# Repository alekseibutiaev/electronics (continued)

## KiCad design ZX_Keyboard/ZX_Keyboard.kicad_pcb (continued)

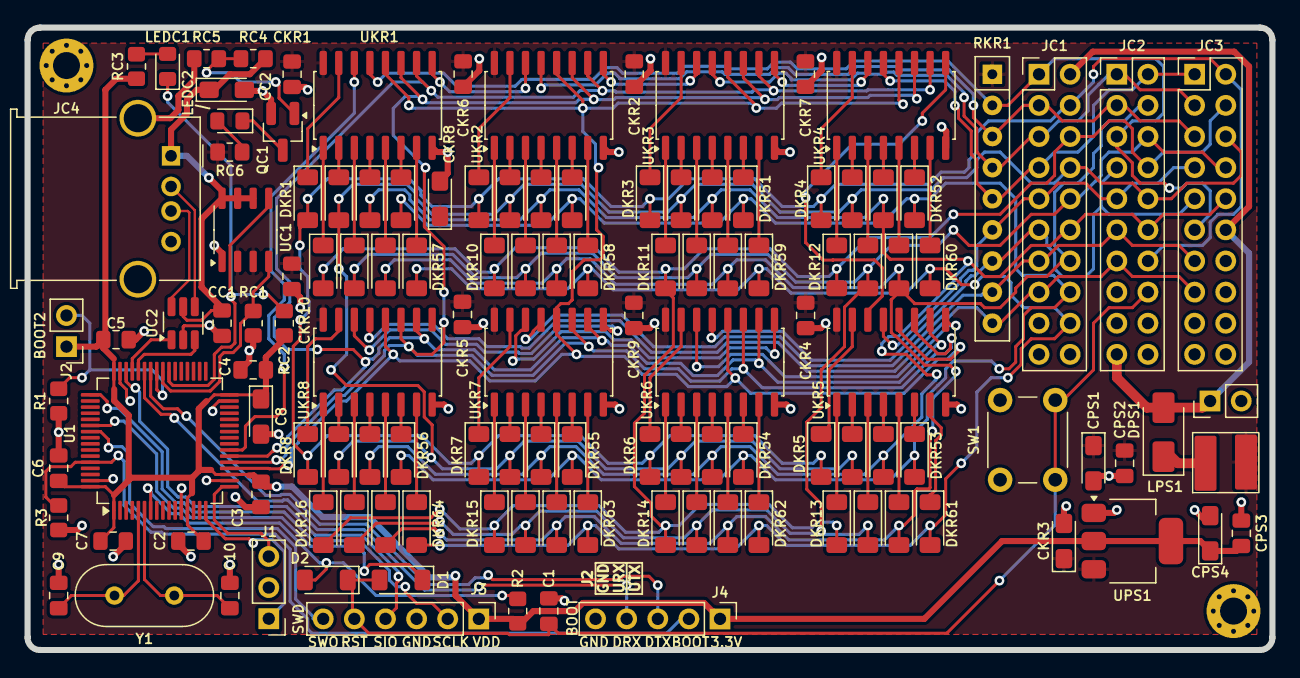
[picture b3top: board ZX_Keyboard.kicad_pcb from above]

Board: 2 copper layers, 101.6 x 50.8 mm, 132 parts (0 on the bottom side), 121 nets.

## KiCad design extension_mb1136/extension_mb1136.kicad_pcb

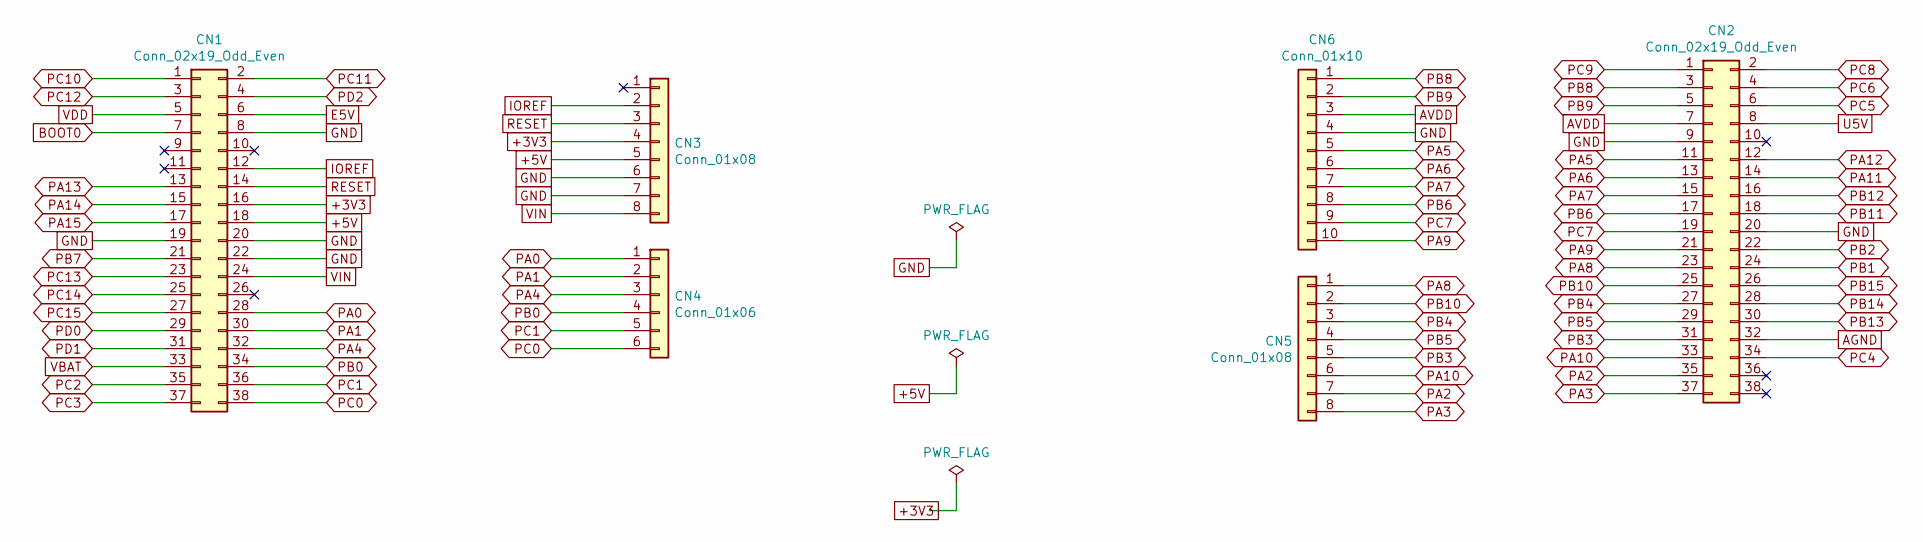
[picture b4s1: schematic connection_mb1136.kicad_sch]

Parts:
CN1, CN2: Conn_02x19_Odd_Even; PinHeader_2x19_P2.54mm_Vertical
CN3, CN5: Conn_01x08; PinSocket_1x08_P2.54mm_Vertical
CN4: Conn_01x06; PinSocket_1x06_P2.54mm_Vertical
CN6: Conn_01x10; PinSocket_1x10_P2.54mm_Vertical

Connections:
+3V3: CN1.16, CN3.4; also elsewhere on the board
+5V: CN1.18, CN3.5; also elsewhere on the board
AGND: CN2.32
AVDD: CN2.7, CN6.3
BOOT0: CN1.7
E5V: CN1.6
GND: CN1.8, CN1.19, CN1.20, CN1.22, CN2.9, CN2.20, CN3.6, CN3.7, CN6.4; also elsewhere on the board
IOREF: CN1.12, CN3.2
PA0: CN1.28, CN4.1
PA1: CN1.30, CN4.2
PA2: CN2.35, CN5.7
PA3: CN2.37, CN5.8
PA4: CN1.32, CN4.3
PA5: CN2.11, CN6.5
PA6: CN2.13, CN6.6
PA7: CN2.15, CN6.7
PA8: CN2.23, CN5.1
PA9: CN2.21, CN6.10; also elsewhere on the board
PA10: CN2.33, CN5.6
PA11: CN2.14; also elsewhere on the board
PA12: CN2.12; also elsewhere on the board
PA13: CN1.13
PA14: CN1.15
PA15: CN1.17
PB0: CN1.34, CN4.4
PB1: CN2.24
PB2: CN2.22
PB3: CN2.31, CN5.5
PB4: CN2.27, CN5.3
PB5: CN2.29, CN5.4
PB6: CN2.17, CN6.8
PB7: CN1.21
PB8: CN2.3, CN6.1
PB9: CN2.5, CN6.2
PB10: CN2.25, CN5.2; also elsewhere on the board
PB11: CN2.18
PB12: CN2.16
PB13: CN2.30
PB14: CN2.28
PB15: CN2.26
PC0: CN1.38, CN4.6
PC1: CN1.36, CN4.5
PC2: CN1.35
PC3: CN1.37
PC4: CN2.34
PC5: CN2.6
PC6: CN2.4
PC7: CN2.19, CN6.9
PC8: CN2.2; also elsewhere on the board
PC9: CN2.1; also elsewhere on the board
PC10: CN1.1
PC11: CN1.2
PC12: CN1.3
PC13: CN1.23
PC14: CN1.25
PC15: CN1.27
PD0: CN1.29
PD1: CN1.31
PD2: CN1.4
RESET: CN1.14, CN3.3
U5V: CN2.8
VBAT: CN1.33
VDD: CN1.5
VIN: CN1.24, CN3.8

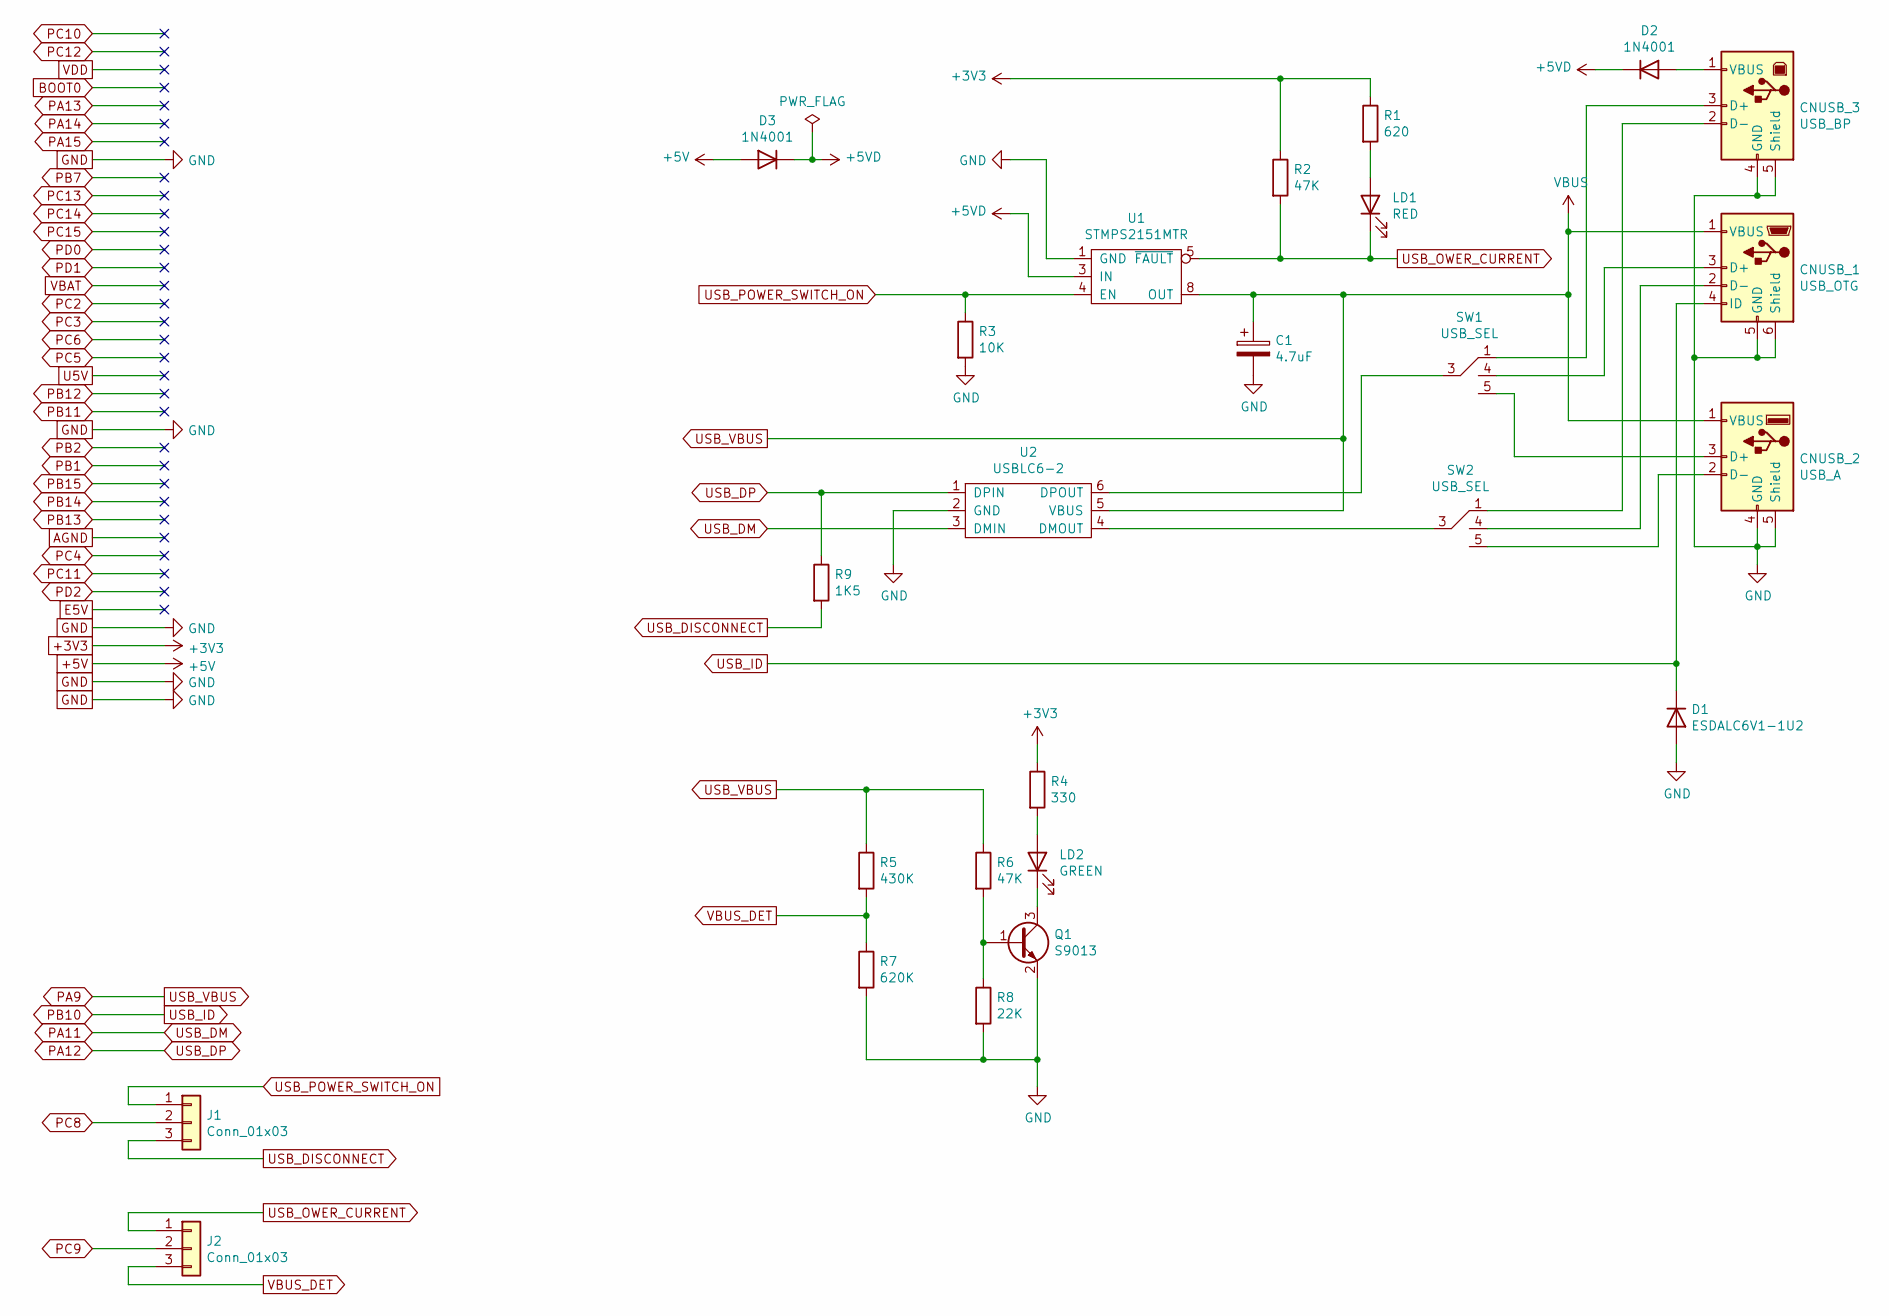
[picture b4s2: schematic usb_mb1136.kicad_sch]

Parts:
C1: 4.7uF; C_1206_3216Metric_Pad1.33x1.80mm_HandSolder
CNUSB_1: USB_OTG; USB_Micro-B_Molex-105017-0001
CNUSB_2: USB_A; USB_A_Molex_67643_Horizontal
CNUSB_3: USB_BP; USB_B_OST_USB-B1HSxx_Horizontal
D1: ESDALC6V1-1U2; D_0201_0603Metric
D2, D3: 1N4001; D_SOD-323_HandSoldering
J1, J2: Conn_01x03; PinHeader_1x03_P2.54mm_Vertical
LD1: RED; D_0805_2012Metric
LD2: GREEN; D_0805_2012Metric
Q1: S9013; SOT-23
R1: 620; R_0805_2012Metric
R2, R6: 47K; R_0805_2012Metric
R3: 10K; R_0805_2012Metric
R4: 330; R_0805_2012Metric
R5: 430K; R_0805_2012Metric
R7: 620K; R_0805_2012Metric
R8: 22K; R_0805_2012Metric
R9: 1K5; R_0805_2012Metric
SW1, SW2: USB_SEL; PinHeader_2x03_P2.54mm_Vertical
U1: STMPS2151MTR; SO-8_3.9x4.9mm_P1.27mm
U2: USBLC6-2; SOT-23-6_Handsoldering

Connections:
+3V3: R1.1, R2.1, R4.1; also elsewhere on the board
+5V: D3.2 (A); also elsewhere on the board
+5VD: D2.1 (K), D3.1 (K), U1.2 (IN), U1.3 (IN)
GND: C1.2, CNUSB_1.5 (GND), CNUSB_1.6 (Shield), CNUSB_2.4 (GND), CNUSB_2.5 (Shield), CNUSB_3.4 (GND), CNUSB_3.5 (Shield), D1.2 (A), Q1.2 (E), R3.2, R7.2, R8.2, U1.1 (GND), U2.2 (GND); also elsewhere on the board
unnamed: CNUSB_1.2 (D-), SW2.4
unnamed: CNUSB_1.3 (D+), SW1.4
unnamed: CNUSB_2.2 (D-), SW2.5
unnamed: CNUSB_2.3 (D+), SW1.5
unnamed: CNUSB_3.1 (VBUS), D2.2 (A)
unnamed: CNUSB_3.2 (D-), SW2.1
unnamed: CNUSB_3.3 (D+), SW1.1
unnamed: LD1.2 (A), R1.2
unnamed: LD2.1 (K), Q1.3 (C)
unnamed: LD2.2 (A), R4.2
unnamed: Q1.1 (B), R6.2, R8.1
unnamed: SW1.3, U2.6 (DPOUT)
unnamed: SW2.3, U2.4 (DMOUT)
PA9: C1.1, CNUSB_1.1 (VBUS), CNUSB_2.1 (VBUS), R5.1, R6.1, U1.6 (OUT), U1.7 (OUT), U1.8 (OUT), U2.5 (VBUS); also elsewhere on the board
PA11: U2.3 (DMIN); also elsewhere on the board
PA12: R9.1, U2.1 (DPIN); also elsewhere on the board
PB10: CNUSB_1.4 (ID), D1.1 (K); also elsewhere on the board
PC8: J1.2; also elsewhere on the board
PC9: J2.2; also elsewhere on the board
USB_DISCONNECT: J1.3, R9.2
USB_OWER_CURRENT: J2.1, LD1.1 (K), R2.2, U1.5 (~FAULT)
USB_POWER_SWITCH_ON: J1.1, R3.1, U1.4 (EN)
VBUS_DET: J2.3, R5.2, R7.1

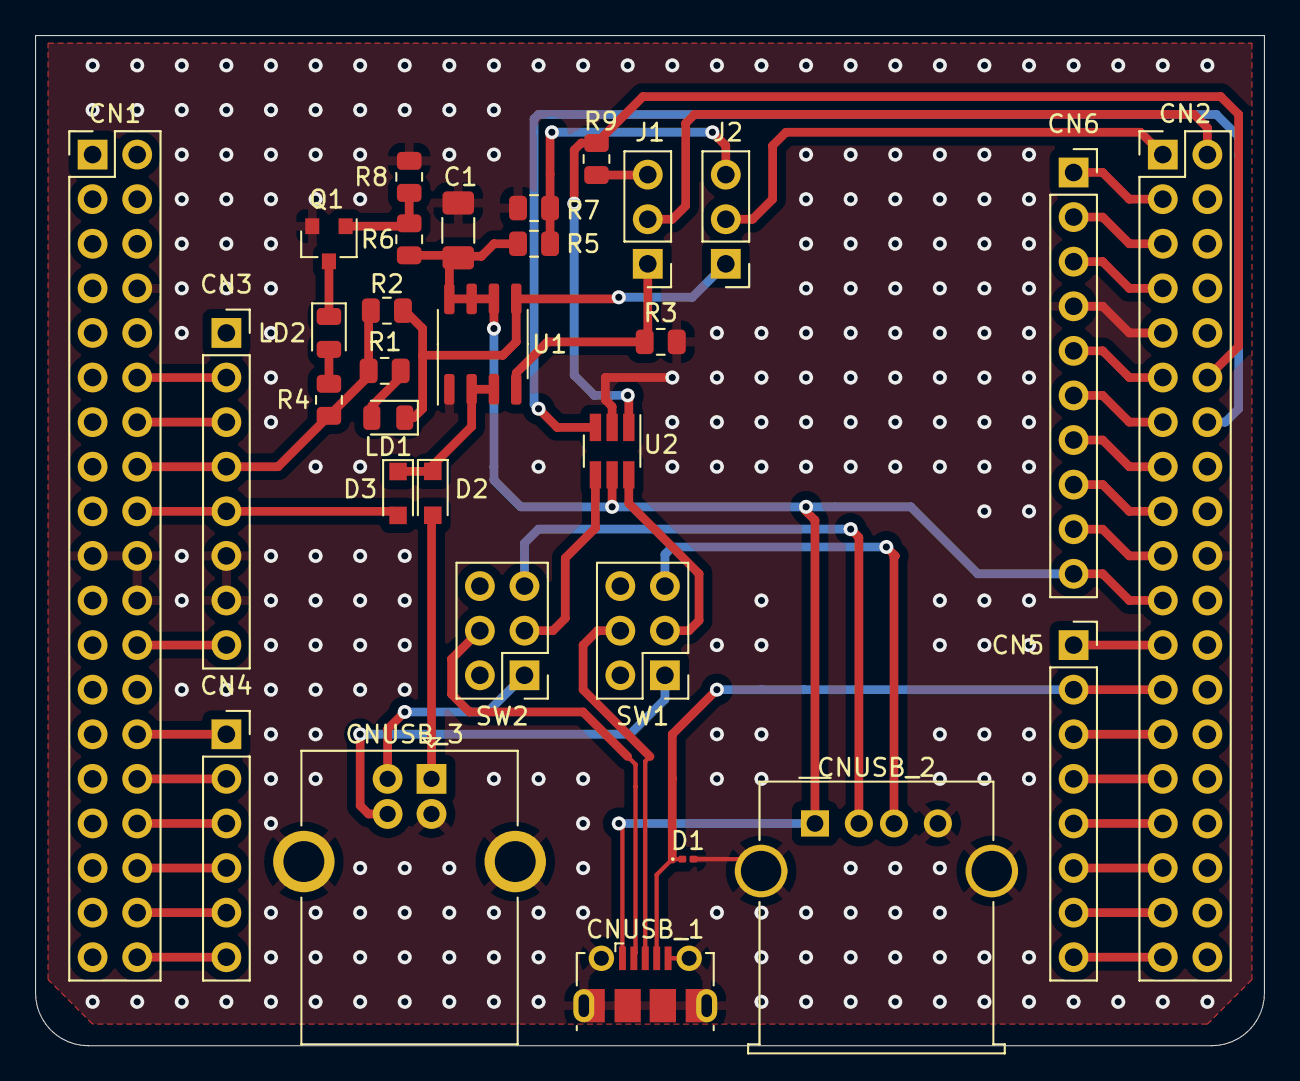
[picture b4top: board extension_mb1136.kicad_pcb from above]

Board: 2 copper layers, 70.0 x 57.5 mm, 31 parts (0 on the bottom side), 51 nets.

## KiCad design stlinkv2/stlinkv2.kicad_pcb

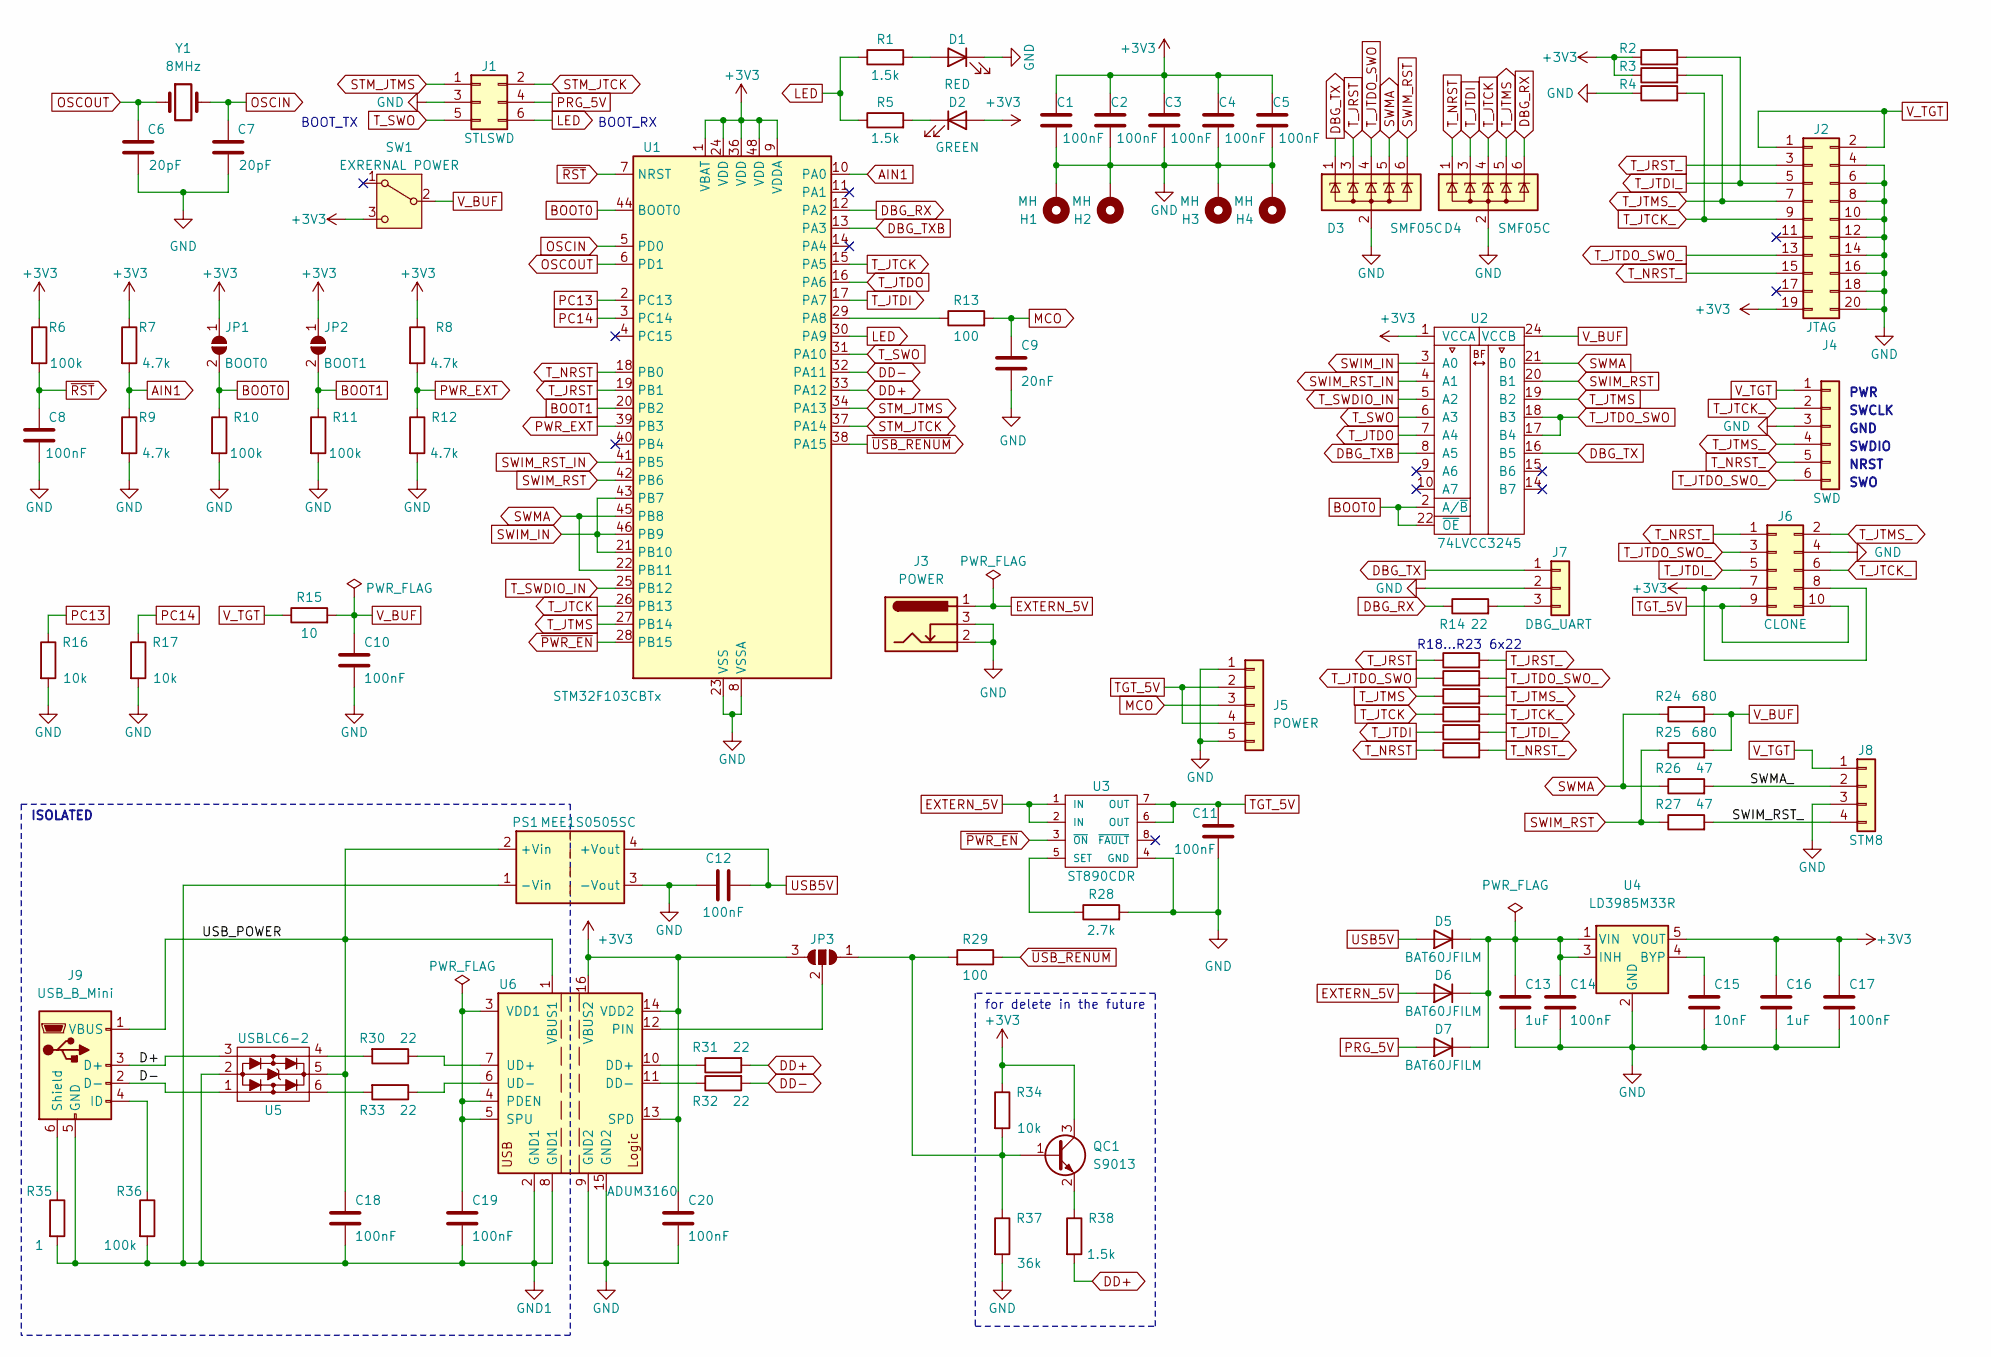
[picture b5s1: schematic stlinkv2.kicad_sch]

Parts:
C1, C2, C3, C4, C5, C8, C10, C11, C12, C14, C17, C18, C19, C20: 100nF; C_0805_2012Metric
C6, C7: 20pF; C_0805_2012Metric
C9: 20nF; C_0805_2012Metric
C13, C16: 1uF; C_0805_2012Metric
C15: 10nF; C_0805_2012Metric
D1: RED; D_0805_2012Metric
D2: GREEN; D_0805_2012Metric
D3, D4: SMF05C; SOT-363_SC-70-6
D5, D6, D7: BAT60JFILM; D_SOD-323_HandSoldering
H1, H2, H3, H4: MH; MountingHole_2.2mm_M2_ISO14580_Pad
J1: STLSWD; PinHeader_2x03_P2.54mm_Vertical
J2: JTAG; IDC-Header_2x10_P2.54mm_Vertical
J3: POWER; 3.5mm power
J4: SWD; PinHeader_1x06_P2.54mm_Vertical
J5: POWER; PinHeader_1x05_P2.54mm_Vertical
J6: CLONE; IDC-Header_2x05_P2.54mm_Vertical
J7: DBG_UART; PinHeader_1x03_P2.54mm_Vertical
J8: STM8; PinHeader_1x04_P2.54mm_Vertical
J9: USB_B_Mini; USB_Mini-B_Wuerth_65100516121_Horizontal
JP1: BOOT0; SolderJumper-2_P1.3mm_Open_TrianglePad1.0x1.5mm
JP2: BOOT1; SolderJumper-2_P1.3mm_Open_TrianglePad1.0x1.5mm
JP3: USB CONTROL; SolderJumper-3_P1.3mm_Open_RoundedPad1.0x1.5mm
PS1: MEE1S0505SC; Converter_DCDC_Murata_MEE1SxxxxSC_THT
QC1: S9013; SOT-23_Handsoldering
R1, R5, R38: 1.5k; R_0805_2012Metric
R2, R3, R4, R16, R17, R34: 10k; R_0805_2012Metric
R6, R10, R11, R36: 100k; R_0805_2012Metric
R7, R8, R9, R12: 4.7k; R_0805_2012Metric
R13, R29: 100; R_0805_2012Metric
R14, R18, R19, R20, R21, R22, R23, R30, R31, R32, R33: 22; R_0805_2012Metric
R15: 10; R_0805_2012Metric
R24, R25: 680; R_0805_2012Metric
R26, R27: 47; R_0805_2012Metric
R28: 2.7k; R_0805_2012Metric
R35: 1; R_0805_2012Metric
R37: 36k; R_0805_2012Metric
SW1: EXRERNAL POWER; SW_SPDT_PCM12
U1: STM32F103CBTx; LQFP-48_7x7mm_P0.5mm
U2: 74LVCC3245; TSSOP-24_4.4x7.8mm_P0.65mm
U3: ST890CDR; SO-8_3.9x4.9mm_P1.27mm
U4: LD3985M33R; SOT-23-5
U5: USBLC6-2; SOT-23-6_Handsoldering
U6: ADUM3160; SOIC-16W_7.5x10.3mm_P1.27mm
Y1: 8MHz; Crystal_HC49-4H_Vertical

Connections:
+3V3: C1.1, C2.1, C3.1, C4.1, C5.1, C16.1, C17.1, C20.1, D2.2 (A), J2.19, J6.7, J6.8, JP1.1 (A), JP2.1 (A), JP3.3 (B), QC1.3 (C), R2.1, R3.1, R6.1, R7.1, R8.1, R34.1, SW1.3 (C), U1.1 (VBAT), U1.9 (VDDA), U1.24 (VDD), U1.36 (VDD), U1.48 (VDD), U2.1 (VCCA), U4.5 (VOUT), U6.13 (SPD), U6.14 (VDD2), U6.16 (VBUS2)
/D+: J9.3 (D+), U5.3
/D-: J9.2 (D-), U5.1
/SWIM_RST_: J8.4, R27.2
/SWMA_: J8.2, R26.2
/USB_POWER: C18.1, J9.1 (VBUS), PS1.2 (+Vin), U5.5, U6.1 (VBUS1)
AIN1: R7.2, R9.1, U1.10 (PA0)
BOOT0: JP1.2 (B), R10.1, U1.44 (BOOT0), U2.2 (A/~B), U2.22 (~OE)
BOOT1: JP2.2 (B), R11.1, U1.20 (PB2)
DBG_RX: D4.6 (K), R14.1, U1.12 (PA2)
DBG_TX: D3.1 (K), J7.1, U2.16 (B5)
DBG_TXB: U1.13 (PA3), U2.8 (A5)
DD+: R31.2, R38.2, U1.33 (PA12)
DD-: R32.2, U1.32 (PA11)
EXTERN_5V: D6.2 (A), J3.1, U3.1 (IN), U3.2 (IN)
GND: C1.2, C2.2, C3.2, C4.2, C5.2, C6.2, C7.2, C8.2, C9.2, C10.2, C11.2, C12.1, C13.2, C14.2, C15.2, C16.2, C17.2, C20.2, D1.1 (K), D3.2 (A), D4.2 (A), H1.1, H2.1, H3.1, H4.1, J1.3, J2.4, J2.6, J2.8, J2.10, J2.12, J2.14, J2.16, J2.18, J2.20, J3.2, J3.3, J4.3, J5.1, J5.5, J6.4, J7.2, J8.3, PS1.3 (-Vout), R4.1, R9.2, R10.2, R11.2, R12.2, R16.2, R17.2, R28.2, R37.2, U1.8 (VSSA), U1.23 (VSS), U1.35 (VSS), U1.47 (VSS), U2.11 (GND), U2.12 (GND), U2.13 (GND), U3.4 (GND), U4.2 (GND), U6.9 (GND2), U6.15 (GND2)
GND1: C18.2, C19.2, J9.5 (GND), PS1.1 (-Vin), R35.2, R36.2, U5.2, U6.2 (GND1), U6.8 (GND1)
LED: J1.6, R1.1, R5.1, U1.30 (PA9)
MCO: C9.1, J5.3, R13.2
unnamed: D1.2 (A), R1.2
unnamed: D2.1 (K), R5.2
unnamed: C13.1, C14.1, D5.1 (K), D6.1 (K), D7.1 (K), U4.1 (VIN), U4.3 (INH)
unnamed: J7.3, R14.2
unnamed: J9.4 (ID), R36.1
unnamed: J9.6 (Shield), R35.1
unnamed: JP3.1 (A), QC1.1 (B), R29.2, R34.2, R37.1
unnamed: JP3.2 (C), U6.12 (PIN)
unnamed: QC1.2 (E), R38.1
unnamed: R30.2, U5.4
unnamed: R33.2, U5.6
unnamed: R13.1, U1.29 (PA8)
unnamed: R28.1, U3.5 (SET)
unnamed: C15.1, U4.4 (BYP)
unnamed: R31.1, U6.10 (DD+)
unnamed: R32.1, U6.11 (DD-)
unnamed: C19.1, U6.3 (VDD1), U6.4 (PDEN), U6.5 (SPU)
unnamed: R30.1, U6.7 (UD+)
unnamed: R33.1, U6.6 (UD-)
OSCIN: C7.1, U1.5 (PD0), Y1.2
OSCOUT: C6.1, U1.6 (PD1), Y1.1
PC13: R16.1, U1.2 (PC13)
PC14: R17.1, U1.3 (PC14)
PRG_5V: D7.2 (A), J1.4
PWR_EXT: R8.2, R12.1, U1.39 (PB3)
STM_JTCK: J1.2, U1.37 (PA14)
STM_JTMS: J1.1, U1.34 (PA13)
SWIM_IN: U1.21 (PB10), U1.43 (PB7), U1.46 (PB9), U2.3 (A0)
SWIM_RST: D3.6 (K), R25.1, R27.1, U1.42 (PB6), U2.20 (B1)
SWIM_RST_IN: U1.41 (PB5), U2.4 (A1)
SWMA: D3.5 (K), R24.1, R26.1, U1.22 (PB11), U1.45 (PB8), U2.21 (B0)
TGT_5V: C11.1, J5.2, J5.4, J6.9, J6.10, U3.6 (OUT), U3.7 (OUT)
T_JRST: D3.3 (K), R18.1, U1.19 (PB1)
T_JRST_: J2.3, R18.2
T_JTCK: D4.4 (K), R21.1, U1.15 (PA5), U1.26 (PB13)
T_JTCK_: J2.9, J4.2, J6.6, R4.2, R21.2
T_JTDI: D4.3 (K), R22.1, U1.17 (PA7)
T_JTDI_: J2.5, J6.5, R2.2, R22.2
T_JTDO: U1.16 (PA6), U2.7 (A4)
T_JTDO_SWO: D3.4 (K), R19.1, U2.17 (B4), U2.18 (B3)
T_JTDO_SWO_: J2.13, J4.6, J6.3, R19.2
T_JTMS: D4.5 (K), R20.1, U1.27 (PB14), U2.19 (B2)
T_JTMS_: J2.7, J4.4, J6.2, R3.2, R20.2
T_NRST: D4.1 (K), R23.1, U1.18 (PB0)
T_NRST_: J2.15, J4.5, J6.1, R23.2
T_SWDIO_IN: U1.25 (PB12), U2.5 (A2)
T_SWO: J1.5, U1.31 (PA10), U2.6 (A3)
USB5V: C12.2, D5.2 (A), PS1.4 (+Vout)
V_BUF: C10.1, R15.2, R24.2, R25.2, SW1.2 (B), U2.24 (VCCB)
V_TGT: J2.1, J2.2, J4.1, J8.1, R15.1
~PWR_EN: U1.28 (PB15), U3.3 (~ON)
~RST: C8.1, R6.2, U1.7 (NRST)
~USB_RENUM: R29.1, U1.38 (PA15)

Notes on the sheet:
BOOT_RX
SWCLK
GND
NRST
R18...R23 6x22
SWDIO
SWO
for delete in the future
PWR
ISOLATED
BOOT_TX

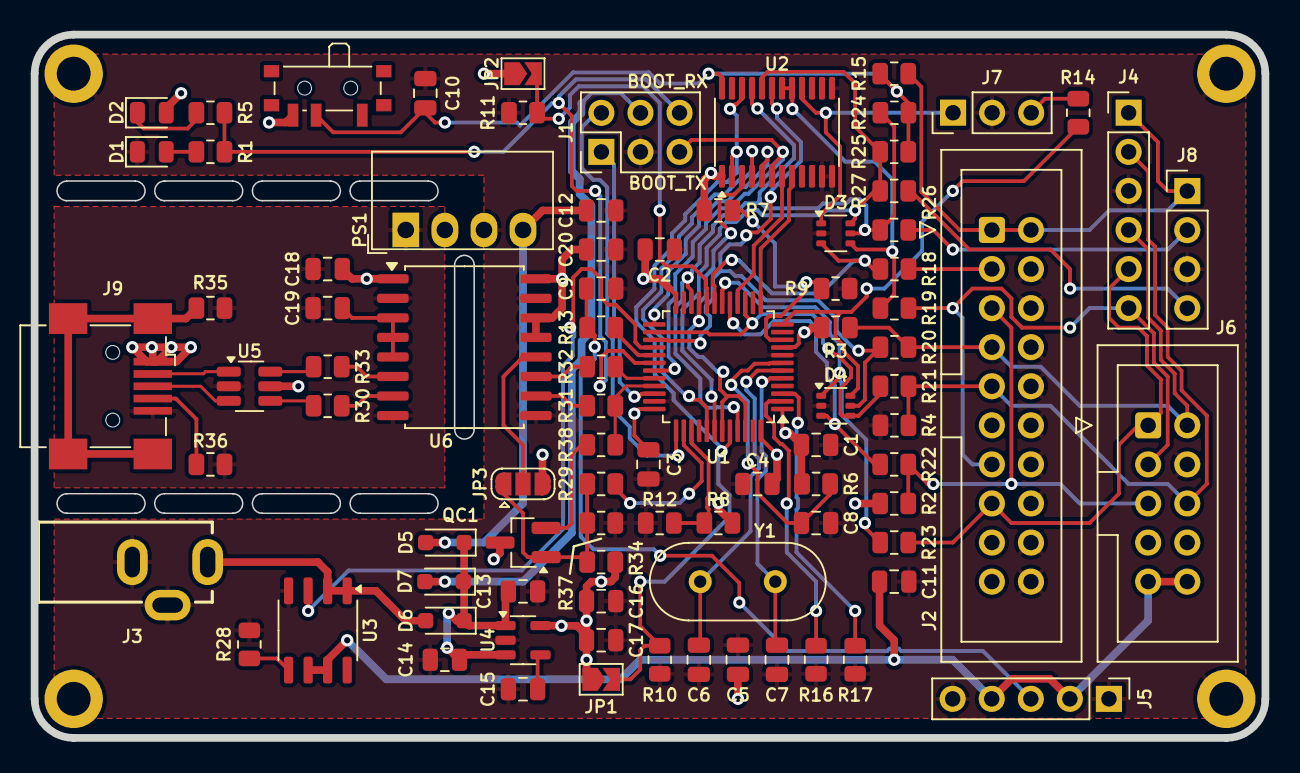
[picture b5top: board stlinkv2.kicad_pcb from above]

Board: 2 copper layers, 80.0 x 45.7 mm, 91 parts (0 on the bottom side), 72 nets.

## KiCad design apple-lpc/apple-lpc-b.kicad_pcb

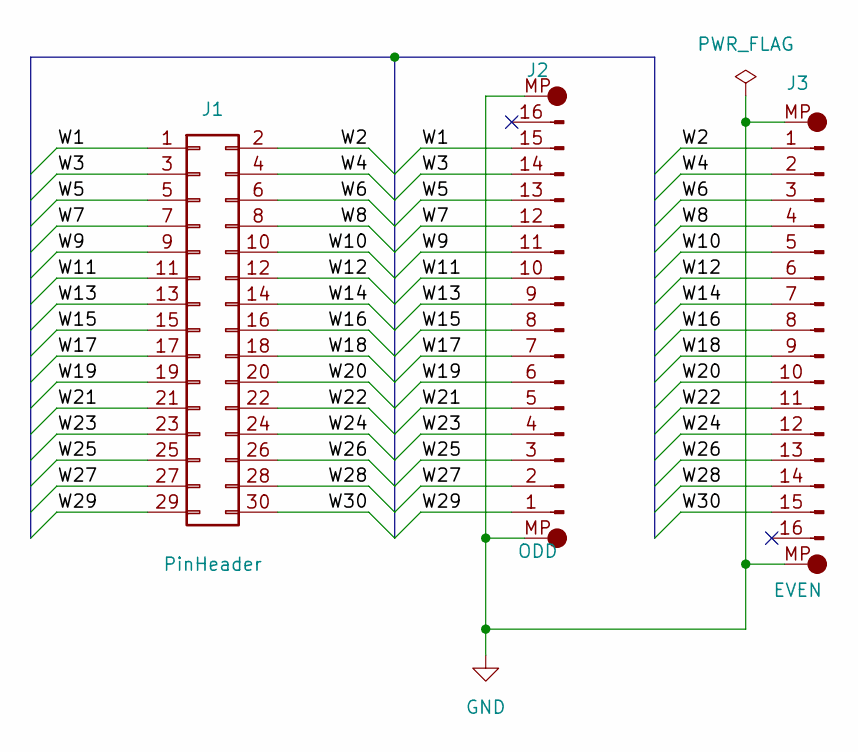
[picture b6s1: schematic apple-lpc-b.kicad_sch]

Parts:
J1: PinHeader; PinHeader_2x15_P2.54mm_Horizontal
J2: ODD; Hirose_FH12-16S-0.5SH_1x16-1MP_P0.50mm_Horizontal
J3: EVEN; Hirose_FH12-16S-0.5SH_1x16-1MP_P0.50mm_Horizontal

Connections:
/W1: J1.1, J2.15
/W2: J1.2, J3.1
/W3: J1.3, J2.14
/W4: J1.4, J3.2
/W5: J1.5, J2.13
/W6: J1.6, J3.3
/W7: J1.7, J2.12
/W8: J1.8, J3.4
/W9: J1.9, J2.11
/W10: J1.10, J3.5
/W11: J1.11, J2.10
/W12: J1.12, J3.6
/W13: J1.13, J2.9
/W14: J1.14, J3.7
/W15: J1.15, J2.8
/W16: J1.16, J3.8
/W17: J1.17, J2.7
/W18: J1.18, J3.9
/W19: J1.19, J2.6
/W20: J1.20, J3.10
/W21: J1.21, J2.5
/W22: J1.22, J3.11
/W23: J1.23, J2.4
/W24: J1.24, J3.12
/W25: J1.25, J2.3
/W26: J1.26, J3.13
/W27: J1.27, J2.2
/W28: J1.28, J3.14
/W29: J1.29, J2.1
/W30: J1.30, J3.15
GND: J2.MP, J3.MP

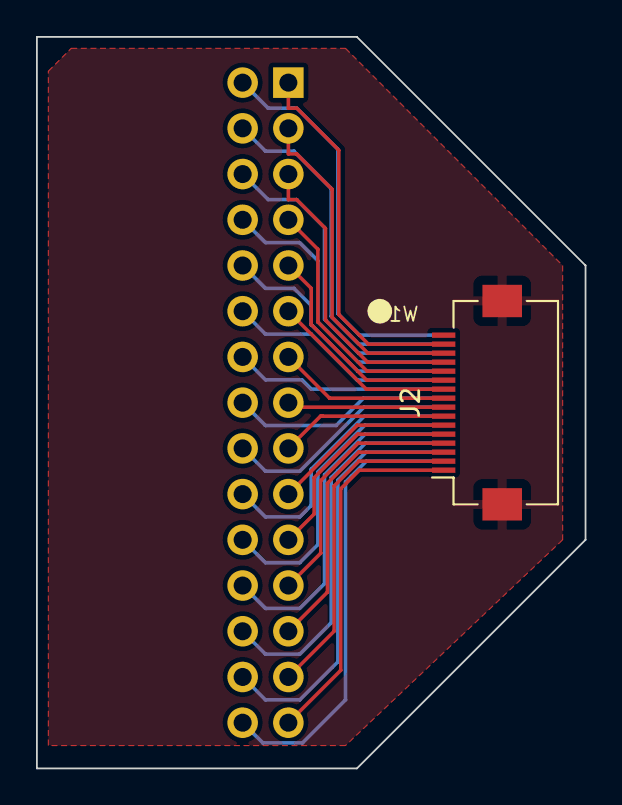
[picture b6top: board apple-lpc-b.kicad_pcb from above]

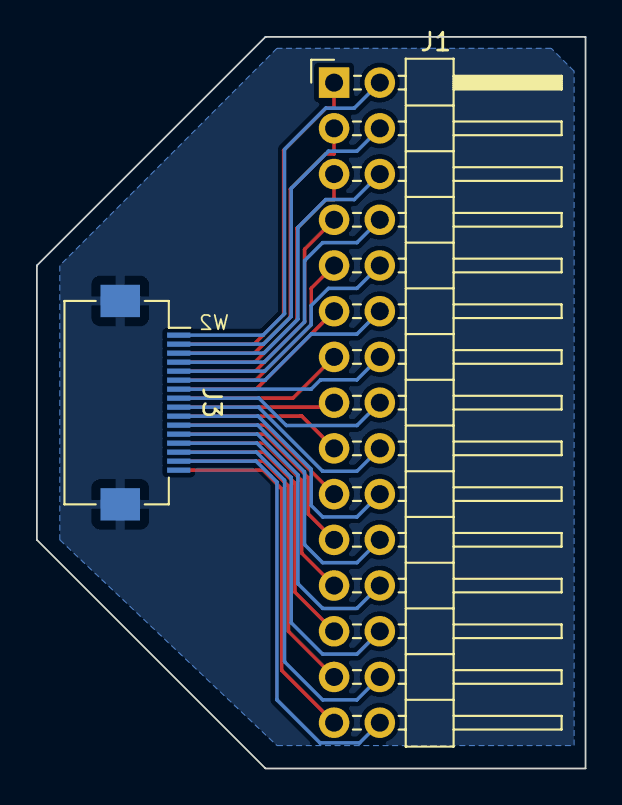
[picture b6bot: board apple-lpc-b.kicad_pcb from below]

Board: 2 copper layers, 30.5 x 40.6 mm, 3 parts (2 on the bottom side), 31 nets.

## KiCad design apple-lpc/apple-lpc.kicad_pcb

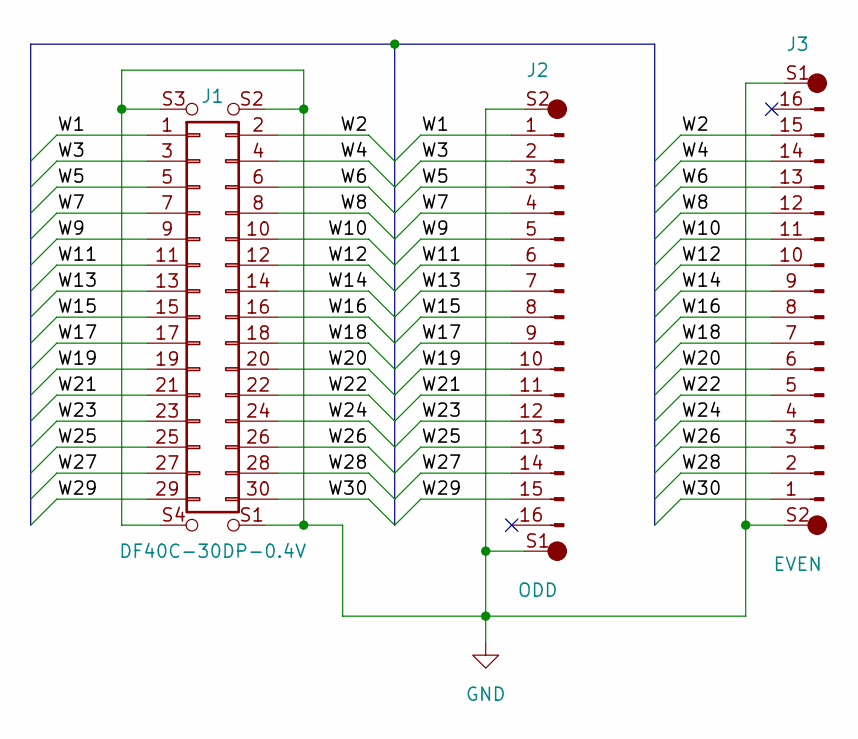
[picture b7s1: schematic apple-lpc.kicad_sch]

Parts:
J1: DF40C-30DP-0.4V; HRS_DF40C-30DP-0.4V_51_
J2: ODD; TE_1-1734742-6
J3: EVEN; TE_1-1734742-6

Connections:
/W1: J1.1, J2.1
/W2: J1.2, J3.15
/W3: J1.3, J2.2
/W4: J1.4, J3.14
/W5: J1.5, J2.3
/W6: J1.6, J3.13
/W7: J1.7, J2.4
/W8: J1.8, J3.12
/W9: J1.9, J2.5
/W10: J1.10, J3.11
/W11: J1.11, J2.6
/W12: J1.12, J3.10
/W13: J1.13, J2.7
/W14: J1.14, J3.9
/W15: J1.15, J2.8
/W16: J1.16, J3.8
/W17: J1.17, J2.9
/W18: J1.18, J3.7
/W19: J1.19, J2.10
/W20: J1.20, J3.6
/W21: J1.21, J2.11
/W22: J1.22, J3.5
/W23: J1.23, J2.12
/W24: J1.24, J3.4
/W25: J1.25, J2.13
/W26: J1.26, J3.3
/W27: J1.27, J2.14
/W28: J1.28, J3.2
/W29: J1.29, J2.15
/W30: J1.30, J3.1
GND: J1.S1 (S2), J1.S2 (S3), J1.S3 (S4), J1.S4 (S1), J2.S1, J2.S2, J3.S1, J3.S2

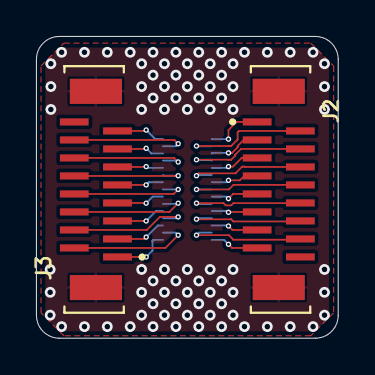
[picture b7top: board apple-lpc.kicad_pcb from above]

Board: 2 copper layers, 16.8 x 16.8 mm, 3 parts (1 on the bottom side), 31 nets.
